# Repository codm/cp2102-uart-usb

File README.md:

# cod.m CP2102N USB UART

---

___Waiting for PCB's! Not yet tested!___

---

This is a reimplementation of [Watterott's CP2102N Breakout](https://learn.watterott.com/breakouts/cp2102n-breakout/) which is licensed under CC-BY-SA.
Based on Silabs CP2102N with integrated voltage regulator for the 3.3V rail.

Never did an own USB UART adapter and wanted to implement USB-C connectors. So I took this oportunity.

Here's a 3D Version for your viewing pleasure: https://a360.co/3vfPNpy

## Features
* USB-C (USB 2.0) connector
* Only 0603 parts, no 0402
* RTS/DSR available as solderpads
* Bigger 3.3V/5V switch
* Power LED

## Features derived from Watterott
* 500mA Polyfuse
* TVS-Diode for USB
* TX/RX LED
* Switchable logic voltage
  * Max 450mA @ 5V, 80mA @ 3.3V
  * Input low level: <= 0.6V
  * Input high level: >= 2.7V

# Thanks
* @watterott CP2102N-Breakout https://github.com/watterott/CP2102N-Breakout
* @AislerHQ for the prototype PCB's

# License
[CC-BY-SA 4.0](https://creativecommons.org/licenses/by-sa/4.0/)

cod.m GmbH, Patrik Mayer, 2022

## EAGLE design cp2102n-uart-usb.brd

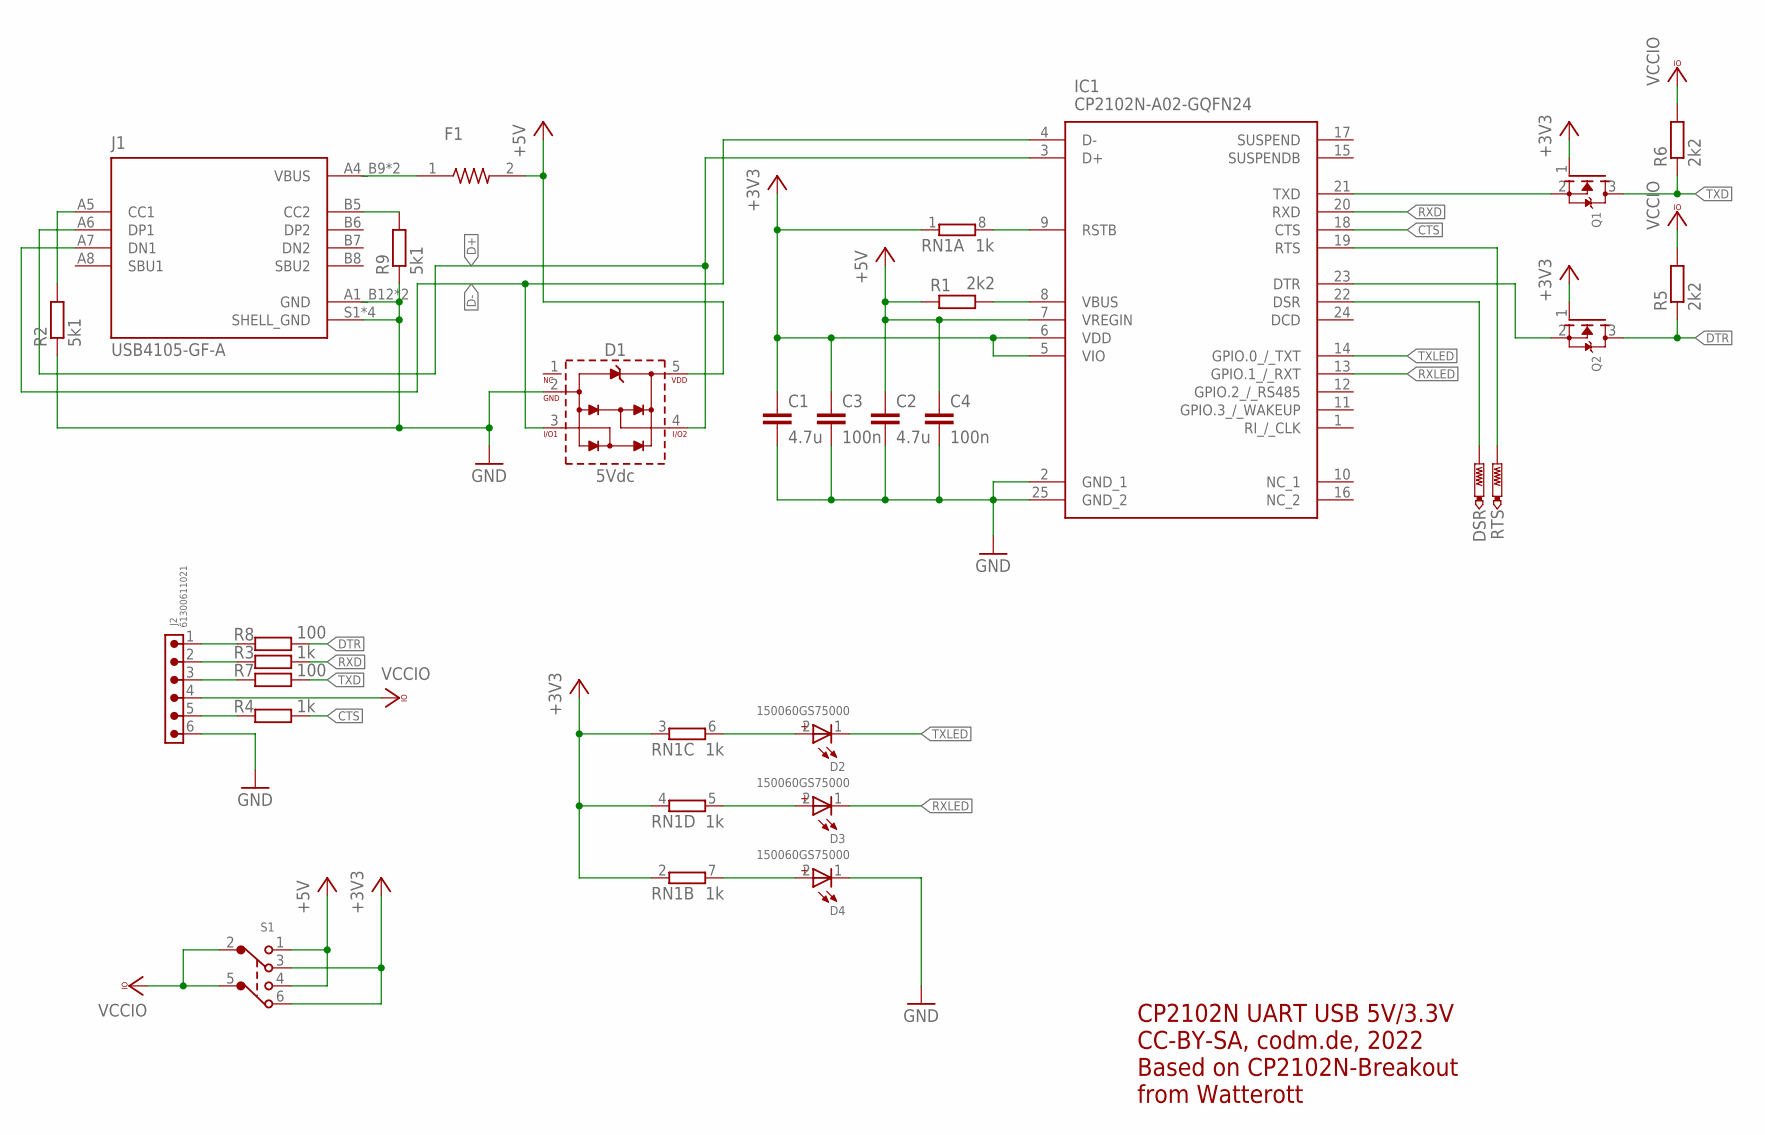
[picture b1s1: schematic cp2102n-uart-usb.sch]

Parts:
C1, C2: 4.7u; C0603K
C3, C4: 100n; C0603K
D1: 5Vdc; WE-TVS_SOT23-5L
D2, D3, D4: 150060GS75000; WL-SMCW_0603
DSR: PTR1B2,54; B2,54
F1: PICOSMDC050S-2; RESC2012X65N
IC1: CP2102N-A02-GQFN24; QFN50P400X400X80-25N
J1: USB4105-GF-A; GCT_USB4105-GF-A
J2: 61300611021
Q1, Q2: MOSFET-NREFLOW; SOT23
R1, R5, R6: 2k2; R0603RF
R2, R9: 5k1; R0603RF
R3, R4: 1k; R0603RF
R7, R8: 100; R0603RF
RN1: 1k; EXB38V
RTS: PTR1B2,54; B2,54
S1: 452403012014

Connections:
+3V3: C1.1, C3.1, IC1.5 (VIO), IC1.6 (VDD), Q1.1 (G), Q2.1 (G), RN1.1, RN1.2 (1), RN1.3 (1), RN1.4 (1), S1.3, S1.6
+5V: C2.1, C4.1, D1.5 (VDD), F1.2, IC1.7 (VREGIN), R1.1, S1.1, S1.4
CTS: IC1.18 (CTS), R4.2
D+: D1.4 (I/O2), IC1.3 (D+), J1.A6 (DP1)
D-: D1.3 (I/O1), IC1.4 (D-), J1.A7 (DN1)
DTR: Q2.3 (D), R5.1, R8.2
GND: C1.2, C2.2, C3.2, C4.2, D1.2 (GND), D4.1 (-), IC1.2 (GND_1), IC1.25 (GND_2), J1.A1_B12 (GND), J1.B1_A12 (GND), J1.S1 (SHELL_GND), J1.S2 (SHELL_GND), J1.S3 (SHELL_GND), J1.S4 (SHELL_GND), J2.6, R2.1, R9.1
unnamed: J1.A5 (CC1), R2.2
unnamed: D3.2 (+), RN1.5 (2)
unnamed: IC1.19 (RTS), RTS.TP
unnamed: D2.2 (+), RN1.6 (2)
unnamed: J1.B5 (CC2), R9.2
unnamed: DSR.TP, IC1.22 (DSR)
unnamed: F1.1, J1.A4_B9 (VBUS), J1.B4_A9 (VBUS)
unnamed: IC1.21 (TXD), Q1.2 (S)
unnamed: IC1.23 (DTR), Q2.2 (S)
unnamed: J2.1, R8.1
unnamed: J2.2, R3.1
unnamed: J2.3, R7.1
unnamed: J2.5, R4.1
unnamed: D4.2 (+), RN1.7 (2)
RSTB: IC1.9 (RSTB), RN1.8 (2)
RXD: IC1.20 (RXD), R3.2
RXLED: D3.1 (-), IC1.13 (GPIO.1_/_RXT)
TXD: Q1.3 (D), R6.1, R7.2
TXLED: D2.1 (-), IC1.14 (GPIO.0_/_TXT)
VBUS: IC1.8 (VBUS), R1.2
VCCIO: J2.4, R5.2, R6.2, S1.2, S1.5

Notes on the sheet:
CP2102N UART USB 5V/3.3V CC-BY-SA, codm.de, 2022 Based on CP2102N-Breakout from Watterott

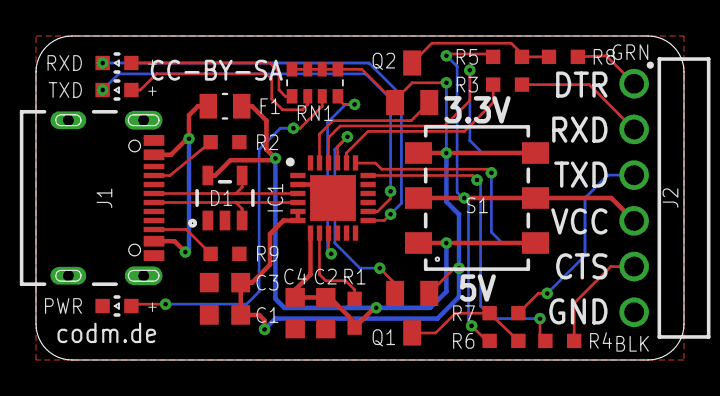
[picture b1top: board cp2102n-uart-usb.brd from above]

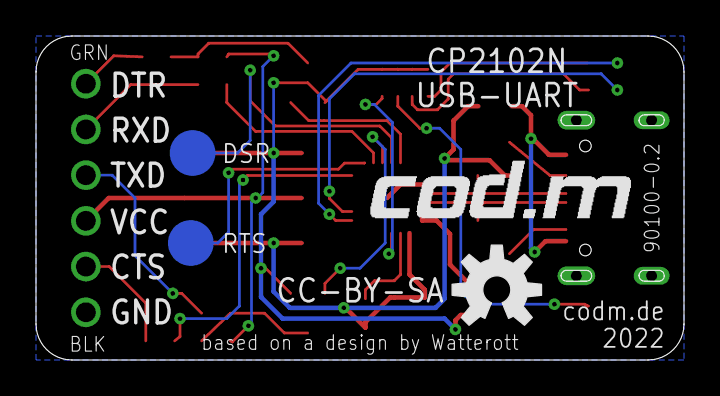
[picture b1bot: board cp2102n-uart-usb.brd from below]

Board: 2 copper layers, 36.0 x 18.0 mm, 29 parts (4 on the bottom side), 28 nets.

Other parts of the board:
U$1: CODM-LOGO
U$2: OSHW-LOGO-M

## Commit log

2022-02-28 first version, prototype ordered
2022-03-11 added 5k1 to CC2
2022-03-11 added schematic pdf
2022-03-11 added readme and images
2022-03-11 added 3d viewer link

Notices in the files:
parts and their libraries:
Eagle_WR-PHD: Copyright: Würth Elektronik
SparkFun-Aesthetics: Licensing: Creative Commons ShareAlike 4.0 International - https://creativecommons.org/licenses/by-sa/4.0
